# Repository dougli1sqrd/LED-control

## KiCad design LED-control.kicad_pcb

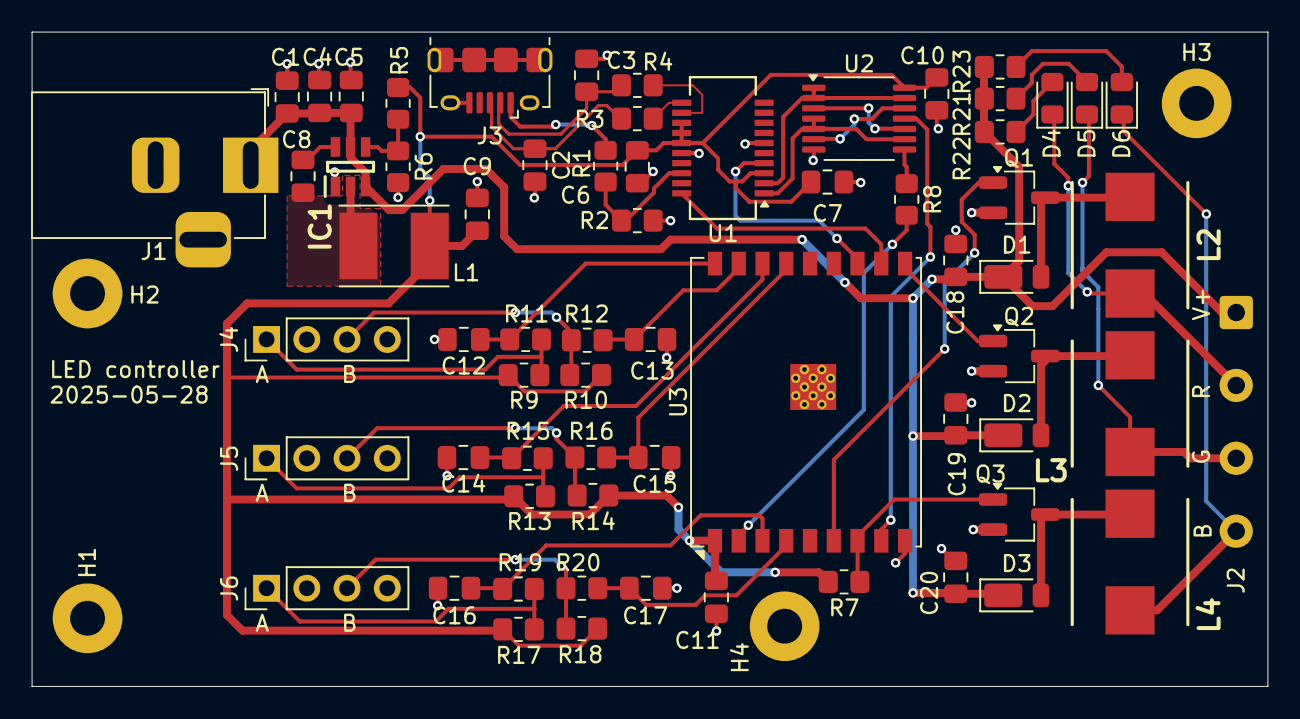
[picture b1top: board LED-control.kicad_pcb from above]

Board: 2 copper layers, 78.0 x 41.3 mm, 70 parts (0 on the bottom side), 45 nets.

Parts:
C1, C4, C18, C19, C20: 10u; C_0805_2012Metric_Pad1.18x1.45mm_HandSolder
C2, C3: 47p; C_0805_2012Metric_Pad1.18x1.45mm_HandSolder
C5, C6, C7, C8, C10, C11, C12, C13, C14, C15, C16, C17: 100n; C_0805_2012Metric_Pad1.18x1.45mm_HandSolder
C9: 47u; C_0805_2012Metric_Pad1.18x1.45mm_HandSolder
D1, D2, D3: D; D_PowerDI-123
D4: Red LED; LED_0805_2012Metric_Pad1.15x1.40mm_HandSolder
D5: Green LED; LED_0805_2012Metric_Pad1.15x1.40mm_HandSolder
D6: Blue LED; LED_0805_2012Metric_Pad1.15x1.40mm_HandSolder
H1, H2, H3, H4: MountingHole_Pad; MountingHole_2.2mm_M2_Pad
IC1: LMR51420XDDCR; SOT95P280X110-6N
J1: Barrel_Jack_MountingPin; BarrelJack_Horizontal
J2: Conn_01x04; SolderWire-0.5sqmm_1x04_P4.6mm_D0.9mm_OD2.1mm
J3: USB_B_Micro; USB_Micro-B_Amphenol_10118194_Horizontal
J4, J5, J6: Conn_01x04; PinHeader_1x04_P2.54mm_Vertical
L1: 10u; L_Taiyo-Yuden_NR-50xx_HandSoldering
L2, L3, L4: 47u; INDPM7973X540N
Q1, Q2, Q3: Q_NMOS_GSD; SC-59_Handsoldering
R1: 4k7; R_0805_2012Metric_Pad1.20x1.40mm_HandSolder
R2, R7, R8, R9, R10, R11, R12, R13, R14, R15, R16, R17, R18, R19, R20: 10k; R_0805_2012Metric_Pad1.20x1.40mm_HandSolder
R3, R4: 27; R_0805_2012Metric_Pad1.20x1.40mm_HandSolder
R5: 100k; R_0805_2012Metric_Pad1.20x1.40mm_HandSolder
R6: 22.1k; R_0805_2012Metric_Pad1.20x1.40mm_HandSolder
R21, R22, R23: 1500; R_0805_2012Metric_Pad1.20x1.40mm_HandSolder
U1: FT231XS; SSOP-20_3.9x8.7mm_P0.635mm
U2: 74HC00; TSSOP-14_4.4x5mm_P0.65mm
U3: ESP32-C3-WROOM-02U

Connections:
/BLUE-: D6.1 (K), J2.4, L4.2
/BLUE_A: C16.1, R19.1, U3.3 (IO4)
/BLUE_B: C17.1, R20.1, U3.4 (IO5)
/BLUE_PWM: Q3.1 (G), R7.1, U3.7 (IO8)
/D+: C2.1, J3.3 (D+), R3.2
/D-: C3.1, J3.2 (D-), R4.2
/GREEN-: D5.1 (K), J2.3, L3.2
/GREEN_A: C14.1, R15.1, U3.16 (IO2)
/GREEN_B: C15.1, R16.1, U3.15 (IO3)
/GREEN_PWM: Q2.1 (G), U3.10 (IO10)
/RED-: D4.1 (K), J2.2, L2.2
/RED_A: C12.1, R11.1, U3.18 (IO0)
/RED_B: C13.1, R12.1, U3.17 (IO1)
/RED_PWM: Q1.1 (G), U3.6 (IO7)
/VBUS: J3.1 (VBUS), R1.2
/VBUS_SENSE: R1.1, R2.1, U1.18 (CBUS0)
/esp32c3/CHIP_EN: R8.2, U3.2 (EN)
/esp32c3/D+: R3.1, U1.11 (USBDP)
/esp32c3/D-: R4.1, U1.12 (USBDM)
/esp32c3/DTR: U1.1 (~DTR), U2.4, U2.5, U2.9
/esp32c3/FB: IC1.4 (FB), R5.2, R6.1
/esp32c3/IO9: U2.11, U3.8 (IO9)
/esp32c3/RTS: U1.2 (~RTS), U2.1, U2.2, U2.13
/esp32c3/RX: U1.20 (TXD), U3.11 (IO20/RXD)
/esp32c3/SW: C8.2, IC1.2 (SW), L1.1
/esp32c3/TX: U1.4 (RXD), U3.12 (IO21/TXD)
GND: C1.2, C2.2, C3.2, C4.2, C5.2, C6.1, C7.2, C9.2, C10.2, C11.1, C12.2, C13.2, C14.2, C15.2, C16.2, C17.2, C18.1, C19.1, C20.1, H1.1, H2.1, H3.1, H4.1, IC1.1 (GND), J1.2, J1.3 (MountPin), J3.5 (GND), J3.6 (Shield), J4.2, J4.4, J5.2, J5.4, J6.2, J6.4, Q1.2 (S), Q2.2 (S), Q3.2 (S), R2.2, R6.2, U1.6 (GND), U1.16 (GND), U2.7 (GND), U3.9 (GND), U3.19 (GND)
unnamed: D1.2 (A), L2.1, Q1.3 (D)
unnamed: D2.2 (A), L3.1, Q2.3 (D)
unnamed: D3.2 (A), L4.1, Q3.3 (D)
unnamed: D4.2 (A), R22.1
unnamed: D5.2 (A), R21.1
unnamed: D6.2 (A), R23.1
unnamed: C8.1, IC1.6 (CB)
unnamed: J4.1, R9.2, R11.2
unnamed: J4.3, R10.2, R12.2
unnamed: J5.1, R13.2, R15.2
unnamed: J5.3, R14.2, R16.2
unnamed: J6.1, R17.2, R19.2
unnamed: J6.3, R18.2, R20.2
unnamed: R8.1, U2.8
unnamed: U2.3, U2.10
unnamed: U2.6, U2.12
VCC: C6.2, C7.1, C9.1, C10.1, C11.2, L1.2, R5.1, R7.2, R9.1, R10.1, R13.1, R14.1, R17.1, R18.1, U1.3 (VCCIO), U1.13 (3V3OUT), U1.14 (~RESET), U1.15 (VCC), U2.14 (VCC), U3.1 (3V3)
Vdrive: C1.1, C4.1, C5.1, C18.2, C19.2, C20.2, D1.1 (K), D2.1 (K), D3.1 (K), IC1.3 (VIN), IC1.5 (EN), J1.1, J2.1, R21.2, R22.2, R23.2

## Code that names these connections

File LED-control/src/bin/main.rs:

#![no_std]
#![no_main]

use esp_backtrace as _;
use esp_hal::delay::Delay;
use esp_hal::gpio::{Input, Pull};
use esp_hal::interrupt::Priority;
use esp_hal::ledc::channel::config::PinConfig;
use esp_hal::ledc::timer::config::Duty;
use esp_hal::ledc::{channel, timer, LSGlobalClkSource, Ledc, LowSpeed};
use esp_hal::peripherals::{Interrupt, Peripherals};
use esp_hal::riscv::asm::wfi;
use esp_hal::timer::timg::{Timer, Timer0, TimerGroup};
use esp_hal::timer::PeriodicTimer;
use esp_hal::{interrupt, prelude::*};
use log::info;
use rotary_encoder_embedded::standard::StandardMode;
use rotary_encoder_embedded::{Direction, RotaryEncoder};

extern crate alloc;

static mut ENCODER: Option<(RotaryEncoder<StandardMode, Input<'_>, Input<'_>>, RotaryEncoder<StandardMode, Input<'_>, Input<'_>>, RotaryEncoder<StandardMode, Input<'_>, Input<'_>>)> = None;

static mut R: u8 = 0;
static mut G: u8 = 0;
static mut B: u8 = 0;

#[entry]
fn main() -> ! {
    let peripherals = esp_hal::init({
        let mut config = esp_hal::Config::default();
        config.cpu_clock = CpuClock::max();
        config
    });

    esp_println::logger::init_logger_from_env();

    esp_alloc::heap_allocator!(72 * 1024);

    let red_pinA = Input::new(peripherals.GPIO0, Pull::Up);
    let red_pinB = Input::new(peripherals.GPIO1, Pull::Up);

    let green_pinA = Input::new(peripherals.GPIO2, Pull::Up);
    let green_pinB = Input::new(peripherals.GPIO3, Pull::Up);

    let blue_pinA = Input::new(peripherals.GPIO4, Pull::Up);
    let blue_pinB = Input::new(peripherals.GPIO5, Pull::Up);

    let red_rotary_encoder = RotaryEncoder::new(red_pinA, red_pinB).into_standard_mode();

    let green_rotary_encoder = RotaryEncoder::new(green_pinA, green_pinB).into_standard_mode();

    let blue_rotary_encoder = RotaryEncoder::new(blue_pinA, blue_pinB).into_standard_mode();

    unsafe {
        ENCODER.replace((red_rotary_encoder, green_rotary_encoder, blue_rotary_encoder));
    }

    let mut led = Ledc::new(peripherals.LEDC);
    led.set_global_slow_clock(LSGlobalClkSource::APBClk);

    let mut pwm_timer = led.timer::<LowSpeed>(timer::Number::Timer1);
    pwm_timer
        .configure(timer::config::Config {
            duty: Duty::Duty12Bit,
            clock_source: timer::LSClockSource::APBClk,
            frequency: 19.kHz(),
        })
        .unwrap();

    let red_pwm = peripherals.GPIO7;
    let green_pwm = peripherals.GPIO10;
    let blue_pwm = peripherals.GPIO8;

    let mut channel0 = led.channel(channel::Number::Channel0, red_pwm);
    channel0
        .configure(channel::config::Config {
            timer: &pwm_timer,
            duty_pct: 0,
            pin_config: PinConfig::PushPull,
        })
        .unwrap();
    let mut channel1 = led.channel(channel::Number::Channel1, green_pwm);
    channel1
        .configure(channel::config::Config {
            timer: &pwm_timer,
            duty_pct: 0,
            pin_config: PinConfig::PushPull,
        })
        .unwrap();

    let mut channel2 = led.channel(channel::Number::Channel2, blue_pwm);
    channel2
        .configure(channel::config::Config {
            timer: &pwm_timer,
            duty_pct: 0,
            pin_config: PinConfig::PushPull,
        })
        .unwrap();

    interrupt::enable(Interrupt::TG0_T0_LEVEL, Priority::Priority1).unwrap();

    let tg = TimerGroup::new(peripherals.TIMG0);
    let timer = tg.timer0;

    timer.set_interrupt_handler(timer_interrupt);
    timer.load_value(1.millis()).unwrap();
    timer.set_auto_reload(true);
    timer.listen();
    timer.start();

    channel0.set_duty_hw(0);
    channel1.set_duty_hw(0);
    channel2.set_duty_hw(0);

    loop {
        let old_red = unsafe { R };
        let old_green = unsafe { G };
        let old_blue = unsafe { B };
        wfi();
        let next_red = unsafe { R };
        if next_red != old_red {
            let next = next_red as u32; //percent: next / 100
            let hw = next * (1 << 12) / 100; // hw: hw / 2^11
            let vis = hw * hw / (1 << 12);
            // info!("{}%, hw: {}, vis: {}", next, hw, vis);
            let _ = channel0.set_duty_hw(vis);
        }
        let next_green = unsafe { G };
        if next_green != old_green {
            let next = next_green as u32; //percent: next / 100
            let hw = next * (1 << 12) / 100; // hw: hw / 2^11
            let vis = hw * hw / (1 << 12);
            // info!("{}%, hw: {}, vis: {}", next, hw, vis);
            let _ = channel1.set_duty_hw(vis);
        }
        let next_blue = unsafe { B };
        if next_blue != old_blue {
            let next = next_blue as u32; //percent: next / 100
            let hw = next * (1 << 12) / 100; // hw: hw / 2^11
            let vis = hw * hw / (1 << 12);
            // info!("{}%, hw: {}, vis: {}", next, hw, vis);
            let _ = channel2.set_duty_hw(vis);
        }
    }
    // for inspiration have a look at the examples at https://github.com/esp-rs/esp-hal/tree/v0.22.0/examples/src/bin
}

#[handler]
fn timer_interrupt() {
    critical_section::with(|_| {
        let timer = unsafe { TimerGroup::new(Peripherals::steal().TIMG0) }.timer0;
        timer.clear_interrupt();
        timer.load_value(1.millis()).unwrap();
        timer.start();

        if let Some((red_encoder, green_encoder, blue_encoder)) = unsafe { &mut ENCODER } {
            match red_encoder.update() {
                Direction::Clockwise => {
                    unsafe { R = R.saturating_add(2).min(100) };
                }
                Direction::Anticlockwise => {
                    unsafe { R = R.saturating_sub(2) };
                }
                Direction::None => {
                    // Do nothing
                }
            }
            match green_encoder.update() {
                Direction::Clockwise => {
                    unsafe { G = G.saturating_add(2).min(100) };
                }
                Direction::Anticlockwise => {
                    unsafe { G = G.saturating_sub(2) };
                }
                Direction::None => {
                    // Do nothing
                }
            }
            match blue_encoder.update() {
                Direction::Clockwise => {
                    unsafe { B = B.saturating_add(2).min(100) };
                }
                Direction::Anticlockwise => {
                    unsafe { B = B.saturating_sub(2) };
                }
                Direction::None => {
                    // Do nothing
                }
            }
        }
    });
}

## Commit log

2025-09-20 first commit, adding gitignore
2025-09-20 adding rest of files
